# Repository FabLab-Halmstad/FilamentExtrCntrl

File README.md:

# FilamentExtrCntrl
Filament Extrusion controller prototype

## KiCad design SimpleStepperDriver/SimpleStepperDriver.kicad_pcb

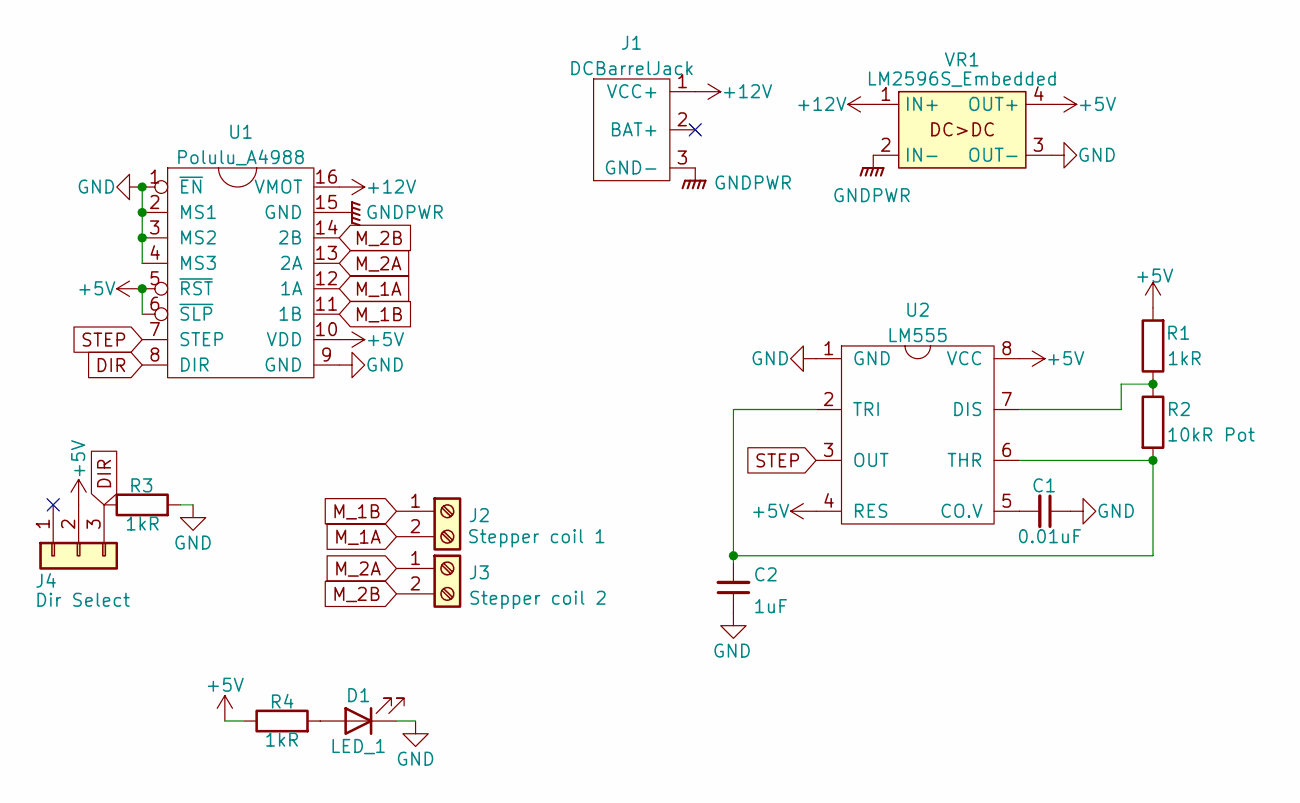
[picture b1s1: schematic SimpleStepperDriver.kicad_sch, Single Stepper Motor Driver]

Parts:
C1: 0.01uF; C_Disc_D3.0mm_W1.6mm_P2.50mm
C2: 1uF; CP_Radial_D5.0mm_P2.50mm
D1: LED_1; LED_D3.0mm
J1: DCBarrelJack; BarrelJack_Horizontal
J2: Stepper coil 1; TerminalBlock_bornier-2_P5.08mm
J3: Stepper coil 2; TerminalBlock_bornier-2_P5.08mm
J4: Dir Select; PinHeader_1x03_P2.54mm_Vertical
R1, R3, R4: 1kR; R_Axial_DIN0204_L3.6mm_D1.6mm_P7.62mm_Horizontal
R2: 10kR Pot; Potentiometer_TT_P0915N
U1: Polulu_A4988; Polulu_A4988_HSocket
U2: LM555; DIP-8_W7.62mm_Socket_LongPads
VR1: LM2596S_Embedded; VoltReg_Embedded_1

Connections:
+5V: J4.2, R1.2, R4.1, U1.5 (~RST), U1.6 (~SLP), U1.10 (VDD), U2.4 (RES), U2.8 (VCC), VR1.4 (OUT+)
+12V: J1.1 (VCC+), U1.16 (VMOT), VR1.1 (IN+)
DIR: J4.3, R3.1, U1.8 (DIR)
GND: C1.1, C2.1, D1.1 (K), R3.2, U1.1 (~EN), U1.2 (MS1), U1.3 (MS2), U1.4 (MS3), U1.9 (GND), U2.1 (GND), VR1.3 (OUT-)
GNDPWR: J1.3 (GND-), U1.15 (GND), VR1.2 (IN-)
M_1A: J2.2, U1.12 (1A)
M_1B: J2.1, U1.11 (1B)
M_2A: J3.1, U1.13 (2A)
M_2B: J3.2, U1.14 (2B)
unnamed: C1.2, U2.5 (CO.V)
unnamed: C2.2, R2.2, U2.2 (TRI), U2.6 (THR)
unnamed: D1.2 (A), R4.2
unnamed: R1.1, R2.1, U2.7 (DIS)
STEP: U1.7 (STEP), U2.3 (OUT)

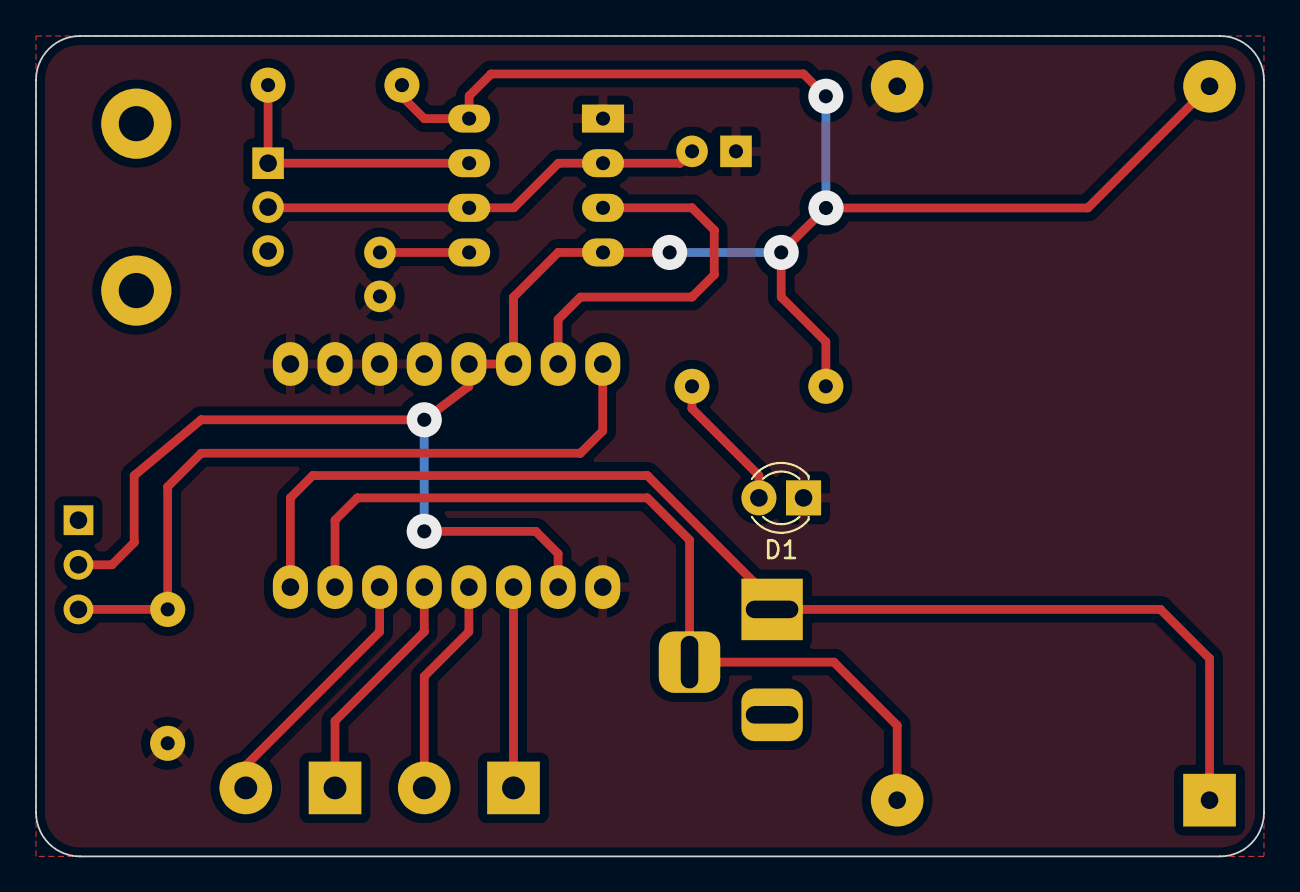
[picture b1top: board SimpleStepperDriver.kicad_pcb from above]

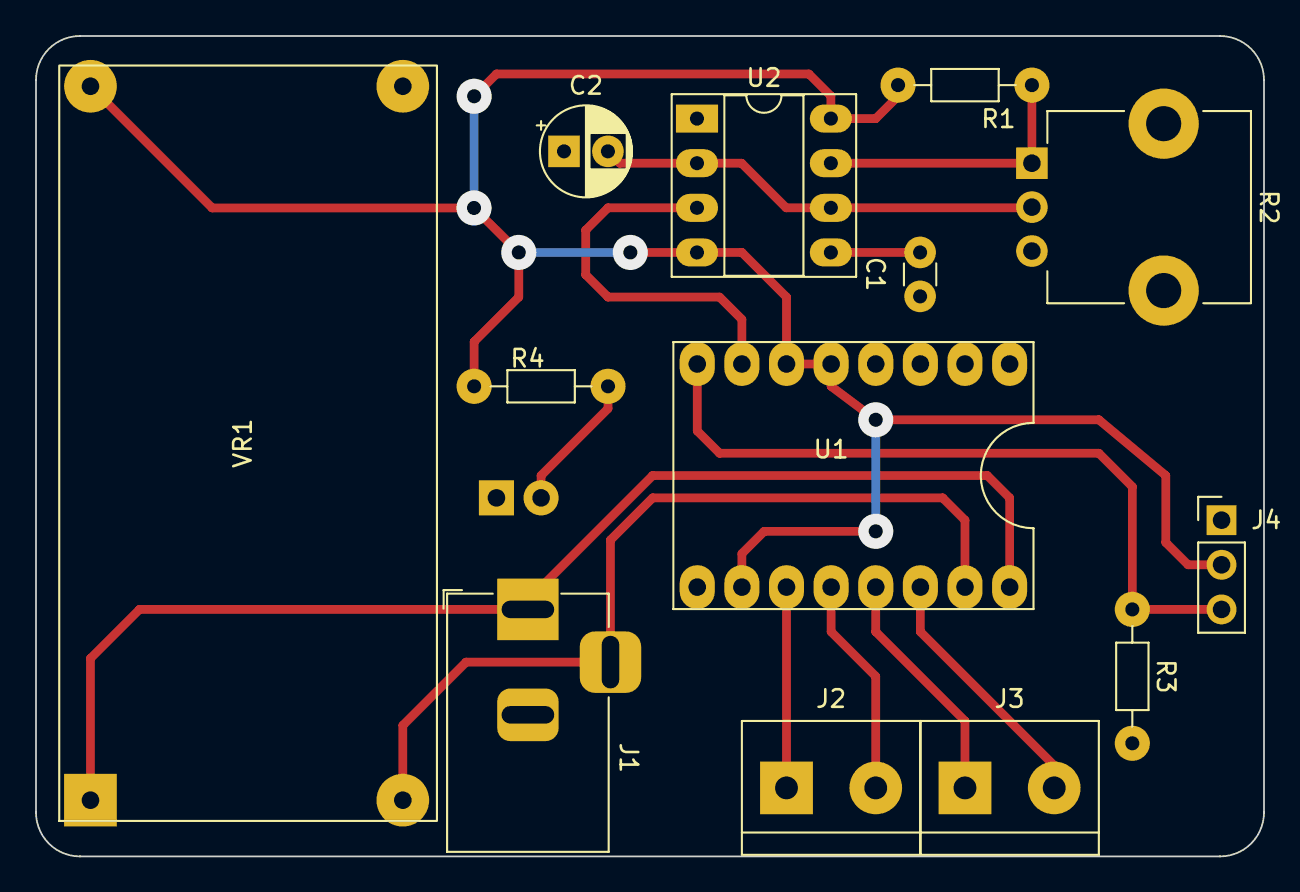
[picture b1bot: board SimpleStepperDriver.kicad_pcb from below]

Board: 2 copper layers, 69.9 x 46.7 mm, 14 parts (13 on the bottom side), 14 nets.
